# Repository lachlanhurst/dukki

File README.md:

# Dukki

> [!IMPORTANT]
> Everything in here is very much a work in progress!

A rework of the Pollen Robotics [Microduck](https://github.com/pollen-robotics/microduck) with a few hardware changes:

- Radxa CM4 brain (instead of the Radxa Zero 3W)
  - RK3576 vs RK3566: roughly twice the CPU and a 6 TOPS NPU vs 0.8 TOPS
- Unitree J288 servos (instead of the Dynamixel XL330-M288-T)
  - About three times faster: 35 rad/s (25 V), vs about 11 rad/s for the XL330
  - Twice the weight: 39 g vs 18 g
  - Similar stall torque, about 0.45 N·m measured against 0.43 N·m for the XL330 model

## Hardware block diagram

## What's in this repository

This repository holds the Dukki documentation, the hardware design files (KiCad), and the code that doesn't fit neatly into one of the forked repos, such as the STM32 servo bridge firmware, compute module setup scripts and J288 bench test tools. Changes elsewhere live on branches of forked repos: the robot firmware in [microduck](https://github.com/lachlanhurst/microduck/tree/dukki) (`dukki`), RL training in [microduck_rl](https://github.com/lachlanhurst/microduck_rl/tree/dukki-j288) (`dukki-j288`), the J288 actuator model in [bam](https://github.com/lachlanhurst/bam/tree/unitree-j288) (`unitree-j288`) and the head IMU driver in [bmi088-rs](https://github.com/lachlanhurst/bmi088-rs/tree/configurable-addresses) (`configurable-addresses`).

## Docs

[Hardware](docs/hardware.md) is the main design document. It covers each subsystem (servos, compute, the STM32 servo bridge, IMUs, power, audio, camera, ToF) and compares it with the OG robot.

[Compute setup](docs/compute-setup.md) takes a Radxa CM4 from the box to a board on WiFi at `microduck.local`. That includes flashing Armbian to the eMMC.

[Servo setup](docs/motor-setup.md) is the bench procedure for each J288 before assembly. You set the bus ID with Unitree's Windows tool, record the firmware version, run a motion check and label the servo for its joint.

[J288 bench testing](docs/j288-testing.md) has the results from characterising one servo: bus timing, friction, armature, torque limits and heating. The main finding is that peak output torque is about 0.45 N·m, close to the XL330.

[Camera setup](docs/camera-setup.md) and [audio setup](docs/audio-setup.md) bring up the IMX219 camera and the MAX98357A speaker and INMP441 microphone on the CM4.

## Licence

MIT, see [LICENSE](LICENSE). The third-party datasheets and schematics in [docs/datasheets/](docs/datasheets/) belong to their publishers and are not covered by it.

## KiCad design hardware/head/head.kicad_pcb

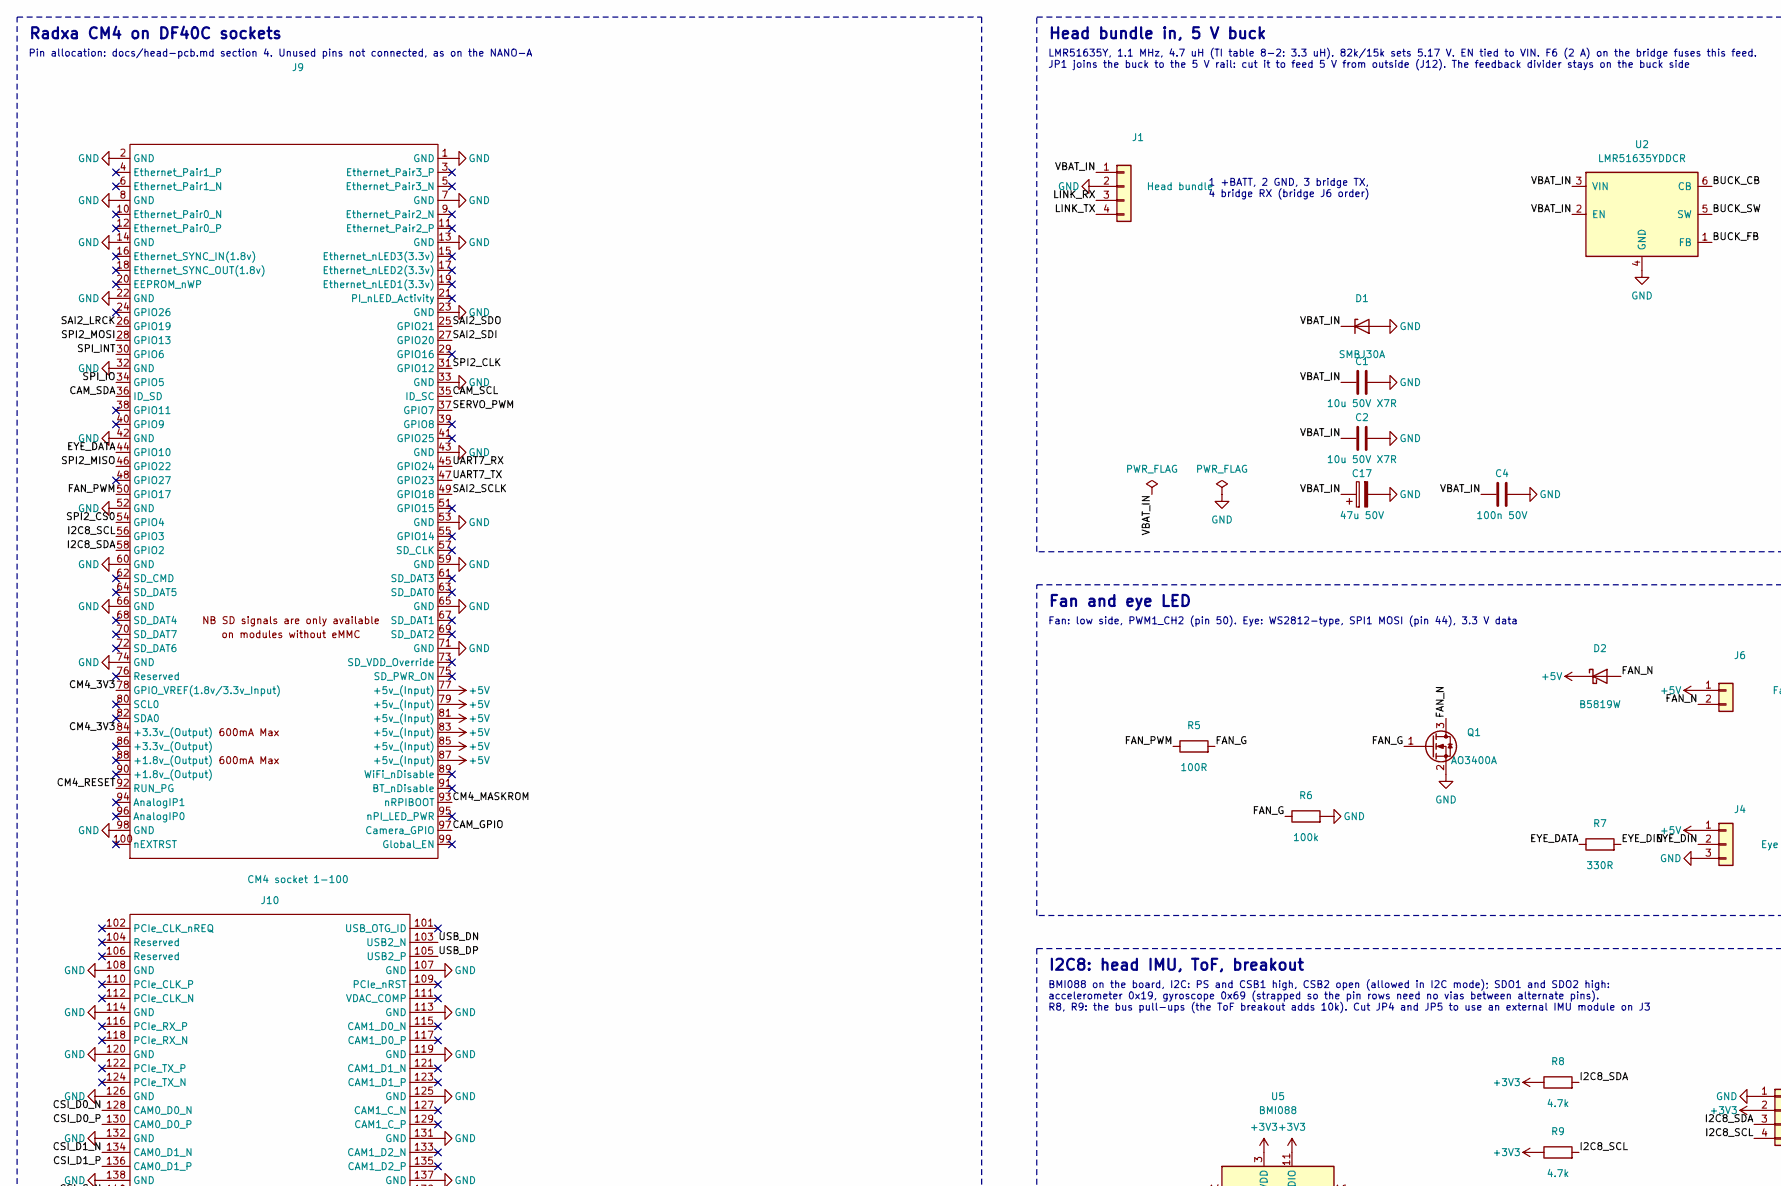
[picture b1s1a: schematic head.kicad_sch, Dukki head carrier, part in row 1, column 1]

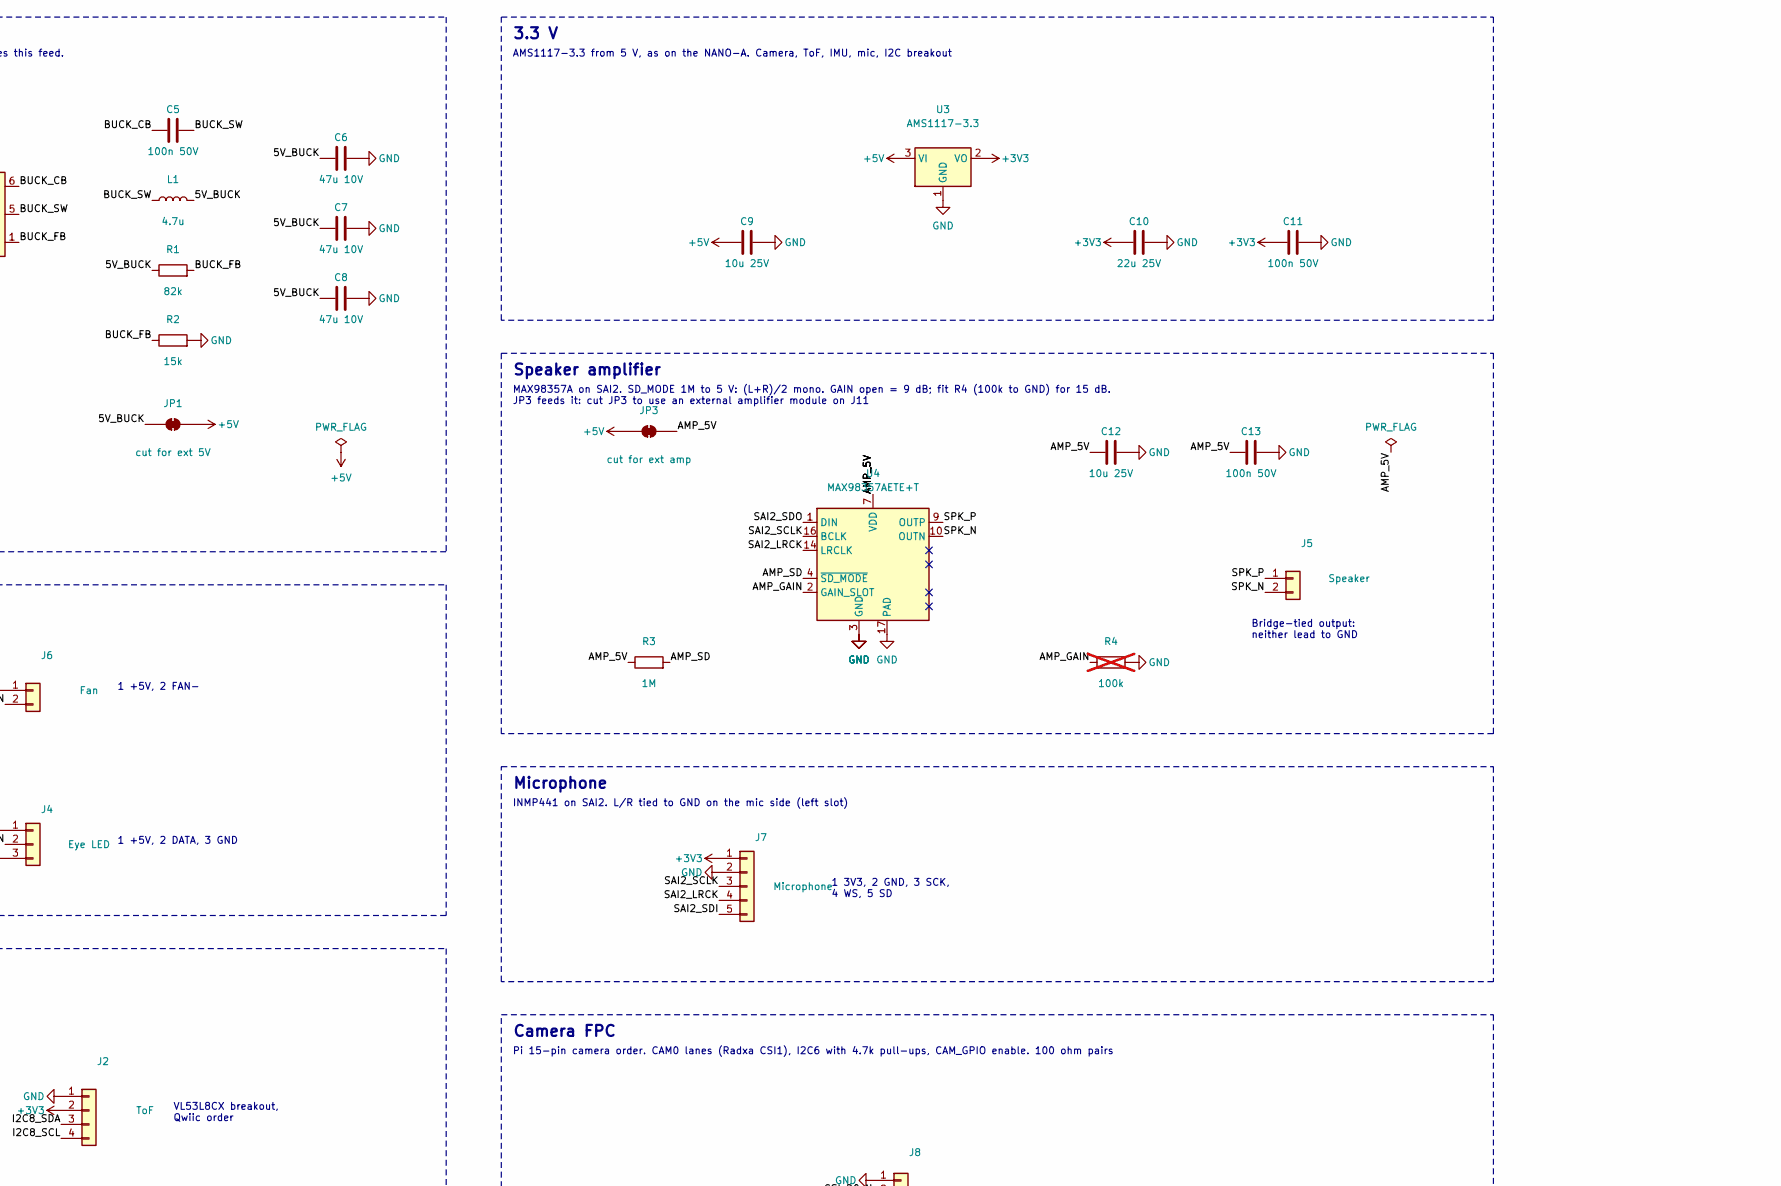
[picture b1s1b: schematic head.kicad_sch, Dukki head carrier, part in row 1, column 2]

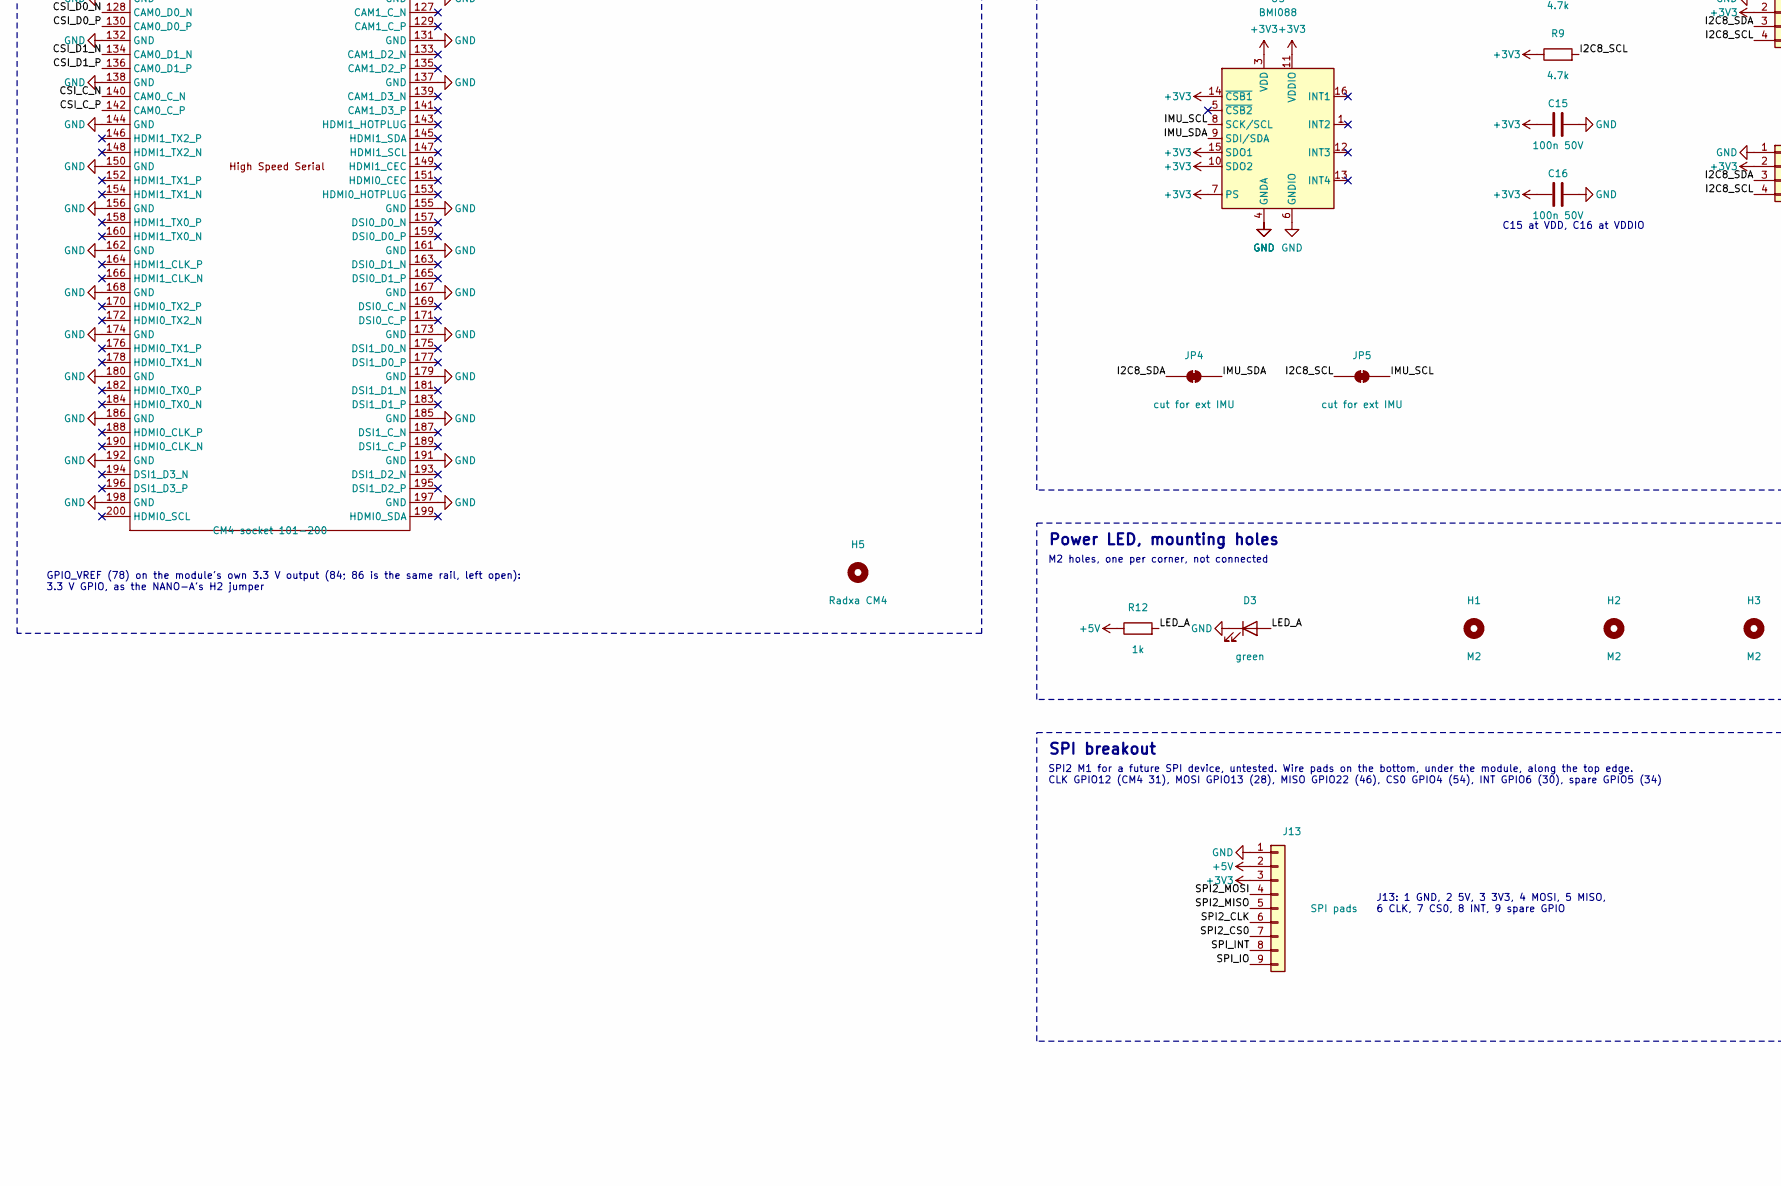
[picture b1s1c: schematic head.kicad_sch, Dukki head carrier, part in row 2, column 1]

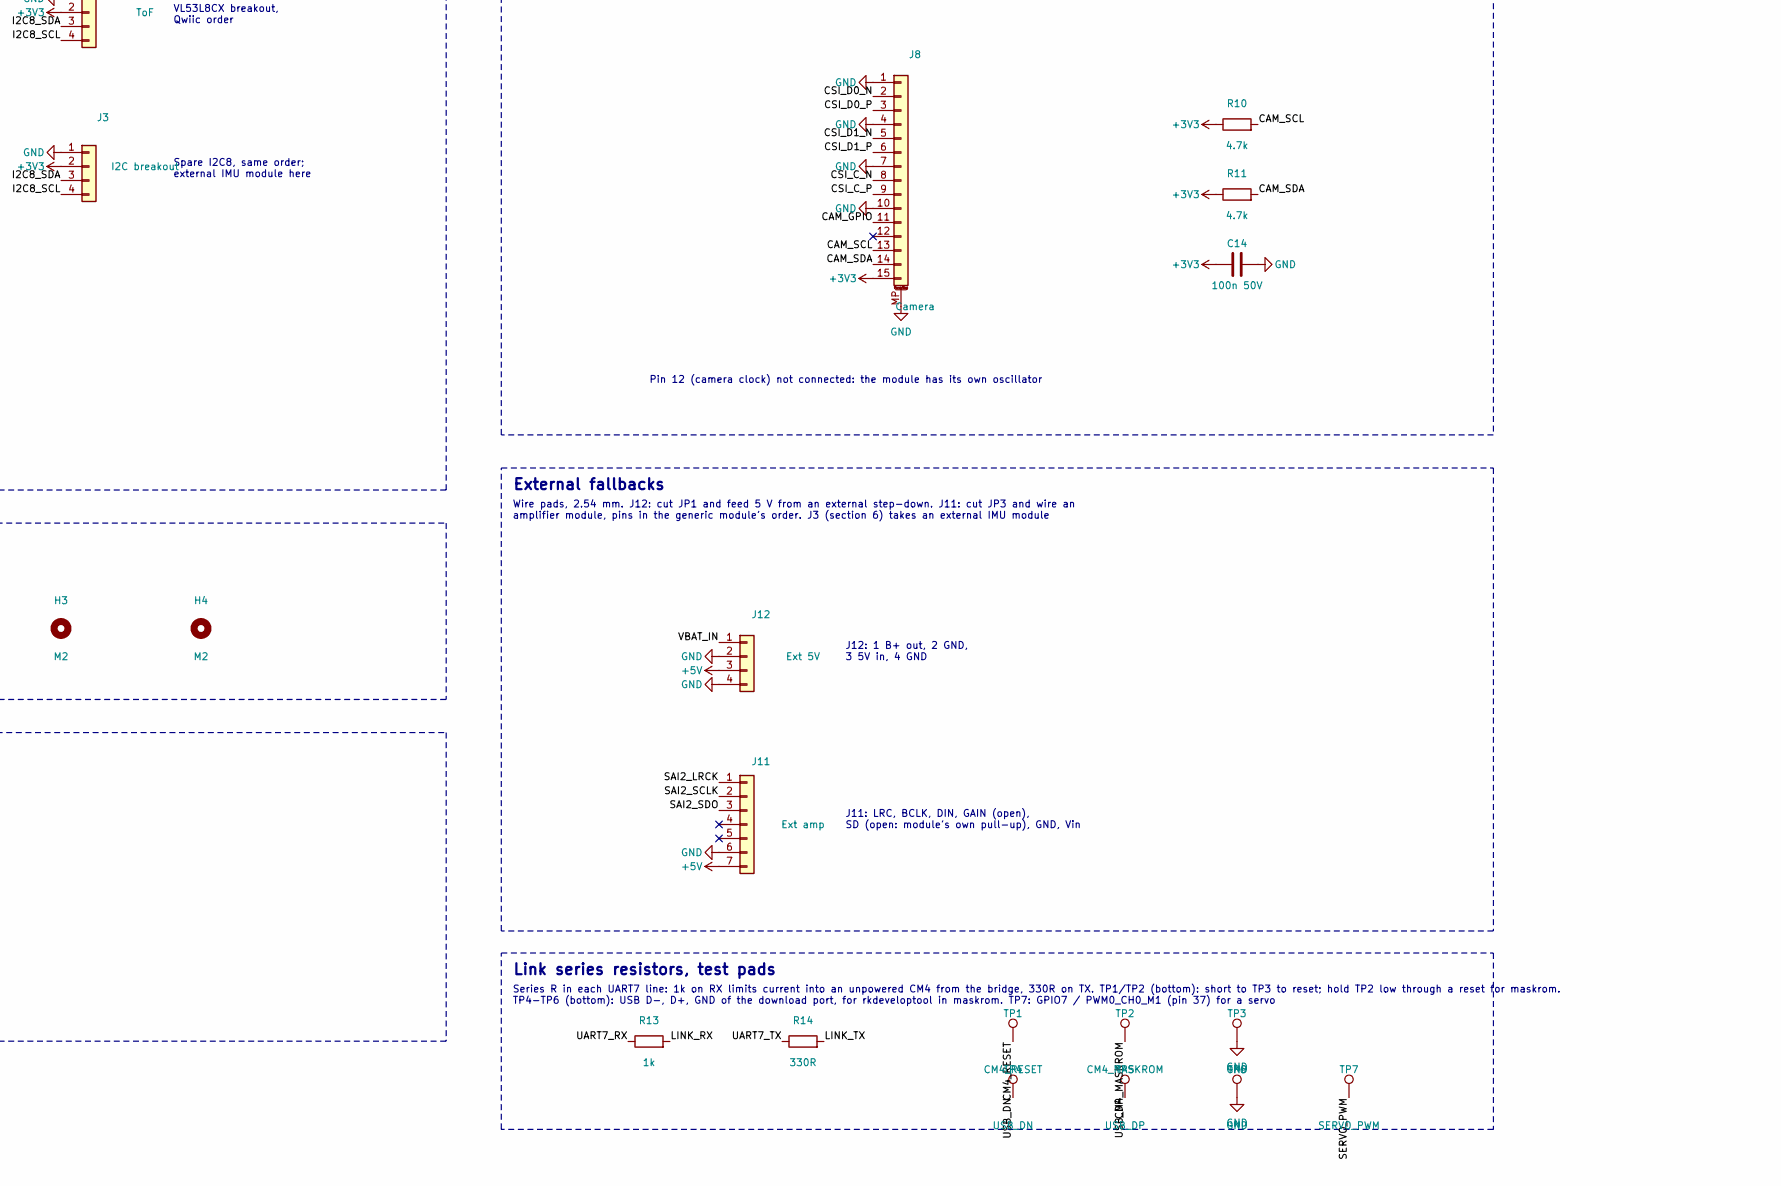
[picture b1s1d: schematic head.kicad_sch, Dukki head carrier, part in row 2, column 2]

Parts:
C1, C2: 10u 50V X7R; C_1210_3225Metric; LCSC C596319
C4, C5, C11, C13, C14, C15, C16: 100n 50V; C_0603_1608Metric; LCSC C14663
C6, C7, C8: 47u 10V; C_1206_3216Metric; LCSC C96123
C9, C12: 10u 25V; C_0805_2012Metric; LCSC C15850
C10: 22u 25V; C_0805_2012Metric; LCSC C45783
C17: 47u 50V; CP_Elec_6.3x7.7; MPN RVT1H470M0607, 47 uF 50 V aluminium, 6.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; LCSC C970679
D1: SMBJ30A; D_SMB; LCSC C19077584
D2: B5819W; D_SOD-123; LCSC C8598
D3: green; LED_0603_1608Metric; LCSC C12624
H1, H2, H3, H4: M2; MountingHole_2.2mm_M2
H5: Radxa CM4; Radxa_CM4_Module
J1: Head bundle; JST_PH_B4B-PH-K_1x04_P2.00mm_Vertical; MPN JST B4B-PH-K-S, through hole, fitted by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
J2: ToF; JST_PH_B4B-PH-K_1x04_P2.00mm_Vertical; MPN JST B4B-PH-K-S, through hole, fitted by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
J3: I2C breakout; JST_PH_B4B-PH-K_1x04_P2.00mm_Vertical; MPN JST B4B-PH-K-S, through hole, fitted by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
J4: Eye LED; JST_PH_B3B-PH-K_1x03_P2.00mm_Vertical; MPN JST B3B-PH-K-S, through hole, fitted by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
J5: Speaker; JST_PH_B2B-PH-K_1x02_P2.00mm_Vertical; MPN JST B2B-PH-K-S, through hole, fitted by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
J6: Fan; JST_PH_B2B-PH-K_1x02_P2.00mm_Vertical; MPN JST B2B-PH-K-S, through hole, fitted by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
J7: Microphone; JST_PH_B5B-PH-K_1x05_P2.00mm_Vertical; MPN JST B5B-PH-K-S, through hole, fitted by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
J8: Camera; FPC_XUNPU_FPC-1.0HF-15PWAR-H20_1x15-1MP_P1.0mm; MPN XUNPU FPC-1.0HF-15PWAR-H20, dual contact; LCSC C19269369
J9: CM4 socket 1-100; DF40C_Socket_CM4_1-100; MPN Hirose DF40C-100DS-0.4V(51); LCSC C597931
J10: CM4 socket 101-200; DF40C_Socket_CM4_101-200; MPN Hirose DF40C-100DS-0.4V(51); LCSC C597931
J11: Ext amp; PinHeader_1x07_P2.54mm_Vertical
J12: Ext 5V; PinHeader_1x04_P2.54mm_Vertical
J13: SPI pads; SolderPads_1x09_P2.54mm_SPI
JP1: cut for ext 5V; SolderJumper-2_Wide_Bridged_3A
JP3: cut for ext amp; SolderJumper-2_Wide_Bridged_3A
JP4, JP5: cut for ext IMU; SolderJumper-2_P1.3mm_Bridged_RoundedPad1.0x1.5mm
L1: 4.7u; L_Sunlord_SWPA6045S; MPN Sunlord SWPA6045S4R7MT, 4.7 uH, 5.5 A s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; LCSC C78804
Q1: AO3400A; SOT-23; LCSC C20917
R1: 82k; R_0603_1608Metric; LCSC C23254
R2: 15k; R_0603_1608Metric; LCSC C22809
R3: 1M; R_0603_1608Metric; LCSC C22935
R4: 100k; R_0603_1608Metric; LCSC C25803; not fitted
R5: 100R; R_0603_1608Metric; LCSC C22775
R6: 100k; R_0603_1608Metric; LCSC C25803
R7, R14: 330R; R_0603_1608Metric; LCSC C23138
R8, R9, R10, R11: 4.7k; R_0603_1608Metric; LCSC C23162
R12, R13: 1k; R_0603_1608Metric; LCSC C21190
TP1: CM4_RESET; TestPoint_Pad_D1.5mm
TP2: CM4_MASKROM; TestPoint_Pad_D1.5mm
TP3, TP6: GND; TestPoint_Pad_D1.5mm
TP4: USB_DN; TestPoint_Pad_D1.5mm
TP5: USB_DP; TestPoint_Pad_D1.5mm
TP7: SERVO_PWM; TestPoint_Pad_D1.5mm
U2: LMR51635YDDCR; TSOT-23-6; LCSC C45262770
U3: AMS1117-3.3; SOT-223-3_TabPin2; LCSC C6186
U4: MAX98357AETE+T; TQFN-16-1EP_3x3mm_P0.5mm_EP1.23x1.23mm; LCSC C910544
U5: BMI088; Bosch_LGA-16_4.5x3mm_P0.5mm_LayoutBorder7x1y_ClockwisePinNu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; LCSC C194919

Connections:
+3V3: C10.1, C11.1, C14.1, C15.1, C16.1, J2.2, J3.2, J7.1, J8.15, J13.3, R8.1, R9.1, R10.1, R11.1, U3.2 (VO), U5.3 (VDD), U5.7 (PS), U5.10 (SDO2), U5.11 (VDDIO), U5.14 (~CSB1), U5.15 (SDO1)
+5V: C9.1, D2.1 (K), J4.1, J6.1, J9.77 (+5v_(Input)), J9.79 (+5v_(Input)), J9.81 (+5v_(Input)), J9.83 (+5v_(Input)), J9.85 (+5v_(Input)), J9.87 (+5v_(Input)), J11.7, J12.3, J13.2, JP1.2 (B), JP3.1 (A), R12.1, U3.3 (VI)
/5V_BUCK: C6.1, C7.1, C8.1, JP1.1 (A), L1.2, R1.1
/AMP_5V: C12.1, C13.1, JP3.2 (B), R3.1, U4.7 (VDD), U4.8 (VDD)
/AMP_GAIN: R4.1, U4.2 (GAIN_SLOT)
/AMP_SD: R3.2, U4.4 (~SD_MODE)
/BUCK_CB: C5.1, U2.6 (CB)
/BUCK_FB: R1.2, R2.1, U2.1 (FB)
/BUCK_SW: C5.2, L1.1, U2.5 (SW)
/CAM_GPIO: J8.11, J9.97 (Camera_GPIO)
/CAM_SCL: J8.13, J9.35 (ID_SC), R10.2
/CAM_SDA: J8.14, J9.36 (ID_SD), R11.2
/CM4_3V3: J9.78 (GPIO_VREF(1.8v/3.3v_Input)), J9.84 (+3.3v_(Output))
/CM4_MASKROM: J9.93 (nRPIBOOT), TP2.1
/CM4_RESET: J9.92 (RUN_PG), TP1.1
/CSI_C_N: J8.8, J10.140 (CAM0_C_N)
/CSI_C_P: J8.9, J10.142 (CAM0_C_P)
/CSI_D0_N: J8.2, J10.128 (CAM0_D0_N)
/CSI_D0_P: J8.3, J10.130 (CAM0_D0_P)
/CSI_D1_N: J8.5, J10.134 (CAM0_D1_N)
/CSI_D1_P: J8.6, J10.136 (CAM0_D1_P)
/EYE_DATA: J9.44 (GPIO10), R7.1
/EYE_DIN: J4.2, R7.2
/FAN_G: Q1.1 (G), R5.2, R6.1
/FAN_N: D2.2 (A), J6.2, Q1.3 (D)
/FAN_PWM: J9.50 (GPIO17), R5.1
/I2C8_SCL: J2.4, J3.4, J9.56 (GPIO3), JP5.1 (A), R9.2
/I2C8_SDA: J2.3, J3.3, J9.58 (GPIO2), JP4.1 (A), R8.2
/IMU_SCL: JP5.2 (B), U5.8 (SCK/SCL)
/IMU_SDA: JP4.2 (B), U5.9 (SDI/SDA)
/LED_A: D3.2 (A), R12.2
/LINK_RX: J1.3, R13.2
/LINK_TX: J1.4, R14.2
/SAI2_LRCK: J7.4, J9.26 (GPIO19), J11.1, U4.14 (LRCLK)
/SAI2_SCLK: J7.3, J9.49 (GPIO18), J11.2, U4.16 (BCLK)
/SAI2_SDI: J7.5, J9.27 (GPIO20)
/SAI2_SDO: J9.25 (GPIO21), J11.3, U4.1 (DIN)
/SERVO_PWM: J9.37 (GPIO7), TP7.1
/SPI2_CLK: J9.31 (GPIO12), J13.6
/SPI2_CS0: J9.54 (GPIO4), J13.7
/SPI2_MISO: J9.46 (GPIO22), J13.5
/SPI2_MOSI: J9.28 (GPIO13), J13.4
/SPI_INT: J9.30 (GPIO6), J13.8
/SPI_IO: J9.34 (GPIO5), J13.9
/SPK_N: J5.2, U4.10 (OUTN)
/SPK_P: J5.1, U4.9 (OUTP)
/UART7_RX: J9.45 (GPIO24), R13.1
/UART7_TX: J9.47 (GPIO23), R14.1
/USB_DN: J10.103 (USB2_N), TP4.1
/USB_DP: J10.105 (USB2_P), TP5.1
/VBAT_IN: C1.1, C2.1, C4.1, C17.1, D1.1 (K), J1.1, J12.1, U2.2 (EN), U2.3 (VIN)
GND: C1.2, C2.2, C4.2, C6.2, C7.2, C8.2, C9.2, C10.2, C11.2, C12.2, C13.2, C14.2, C15.2, C16.2, C17.2, D1.2 (A), D3.1 (K), J1.2, J2.1, J3.1, J4.3, J7.2, J8.1, J8.4, J8.7, J8.10, J8.MP (MountPin), J9.1 (GND), J9.2 (GND), J9.7 (GND), J9.8 (GND), J9.13 (GND), J9.14 (GND), J9.22 (GND), J9.23 (GND), J9.32 (GND), J9.33 (GND), J9.42 (GND), J9.43 (GND), J9.52 (GND), J9.53 (GND), J9.59 (GND), J9.60 (GND), J9.65 (GND), J9.66 (GND), J9.71 (GND), J9.74 (GND), J9.98 (GND), J10.107 (GND), J10.108 (GND), J10.113 (GND), J10.114 (GND), J10.119 (GND), J10.120 (GND), J10.125 (GND), J10.126 (GND), J10.131 (GND), J10.132 (GND), J10.137 (GND), J10.138 (GND), J10.144 (GND), J10.150 (GND), J10.155 (GND), J10.156 (GND), J10.161 (GND), J10.162 (GND), J10.167 (GND), J10.168 (GND), J10.173 (GND), J10.174 (GND), J10.179 (GND), J10.180 (GND), J10.185 (GND), J10.186 (GND), J10.191 (GND), J10.192 (GND), J10.197 (GND), J10.198 (GND), J11.6, J12.2, J12.4, J13.1, Q1.2 (S), R2.2, R4.2, R6.2, TP3.1, TP6.1, U2.4 (GND), U3.1 (GND), U4.3 (GND), U4.11 (GND), U4.15 (GND), U4.17 (PAD), U5.2 (GNDA), U5.4 (GNDA), U5.6 (GNDIO)

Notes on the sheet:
Radxa CM4 on DF40C sockets
Pin allocation: docs/head-pcb.md section 4. Unused pins not connected, as on the NANO-A
GPIO_VREF (78) on the module's own 3.3 V output (84; 86 is the same rail, left open): 3.3 V GPIO, as the NANO-A's H2 jumper
Head bundle in, 5 V buck
LMR51635Y, 1.1 MHz, 4.7 uH (TI table 8-2: 3.3 uH). 82k/15k sets 5.17 V. EN tied to VIN. F6 (2 A) on the bridge fuses this feed. JP1 joins the buck to the 5 V rail: cut it to feed 5 V from outside (J12). The feedback divider stays on the buck side
1 +BATT, 2 GND, 3 bridge TX, 4 bridge RX (bridge J6 order)
3.3 V
AMS1117-3.3 from 5 V, as on the NANO-A. Camera, ToF, IMU, mic, I2C breakout
Speaker amplifier
MAX98357A on SAI2. SD_MODE 1M to 5 V: (L+R)/2 mono. GAIN open = 9 dB; fit R4 (100k to GND) for 15 dB. JP3 feeds it: cut JP3 to use an external amplifier module on J11
Bridge-tied output: neither lead to GND
Fan and eye LED
Fan: low side, PWM1_CH2 (pin 50). Eye: WS2812-type, SPI1 MOSI (pin 44), 3.3 V data
1 +5V, 2 FAN-
1 +5V, 2 DATA, 3 GND
I2C8: head IMU, ToF, breakout
BMI088 on the board, I2C: PS and CSB1 high, CSB2 open (allowed in I2C mode); SDO1 and SDO2 high: accelerometer 0x19, gyroscope 0x69 (strapped so the pin rows need no vias between alternate pins). R8, R9: the bus pull-ups (the ToF breakout adds 10k). Cut JP4 and JP5 to use an external IMU module on 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
C15 at VDD, C16 at VDDIO
VL53L8CX breakout, Qwiic order
Spare I2C8, same order; external IMU module here
Microphone
INMP441 on SAI2. L/R tied to GND on the mic side (left slot)
1 3V3, 2 GND, 3 SCK, 4 WS, 5 SD
Camera FPC
Pi 15-pin camera order. CAM0 lanes (Radxa CSI1), I2C6 with 4.7k pull-ups, CAM_GPIO enable. 100 ohm pairs
Pin 12 (camera clock) not connected: the module has its own oscillator
Power LED, mounting holes
M2 holes, one per corner, not connected
External fallbacks
Wire pads, 2.54 mm. J12: cut JP1 and feed 5 V from an external step-down. J11: cut JP3 and wire an amplifier module, pins in the generic module's order. J3 (section 6) takes an external IMU module
J12: 1 B+ out, 2 GND, 3 5V in, 4 GND
J11: LRC, BCLK, DIN, GAIN (open), SD (open: module's own pull-up), GND, Vin
SPI breakout
SPI2 M1 for a future SPI device, untested. Wire pads on the bottom, under the module, along the top edge. CLK GPIO12 (CM4 31), MOSI GPIO13 (28), MISO GPIO22 (46), CS0 GPIO4 (54), INT GPIO6 (30), spare GPIO5 (34)
J13: 1 GND, 2 5V, 3 3V3, 4 MOSI, 5 MISO, 6 CLK, 7 CS0, 8 INT, 9 spare GPIO
Link series resistors, test pads
Series R in each UART7 line: 1k on RX limits current into an unpowered CM4 from the bridge, 330R on TX. TP1/TP2 (bottom): short to TP3 to reset; hold TP2 low through a reset for maskrom. TP4-TP6 (bottom): USB D-, D+, GND of the download port, for rkdeveloptool in maskrom. TP7: GPIO7 / PWM0_CH0_M1 (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

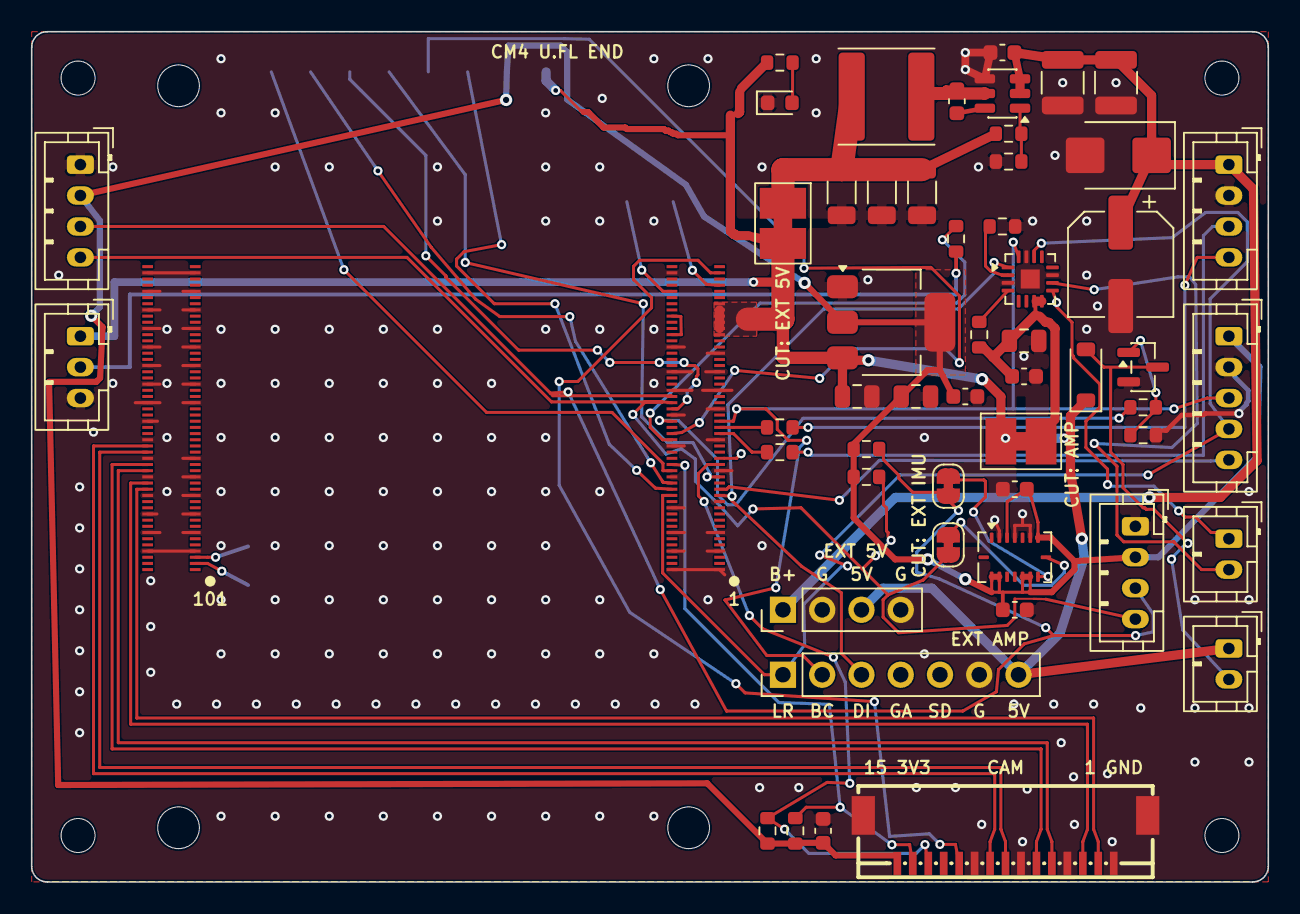
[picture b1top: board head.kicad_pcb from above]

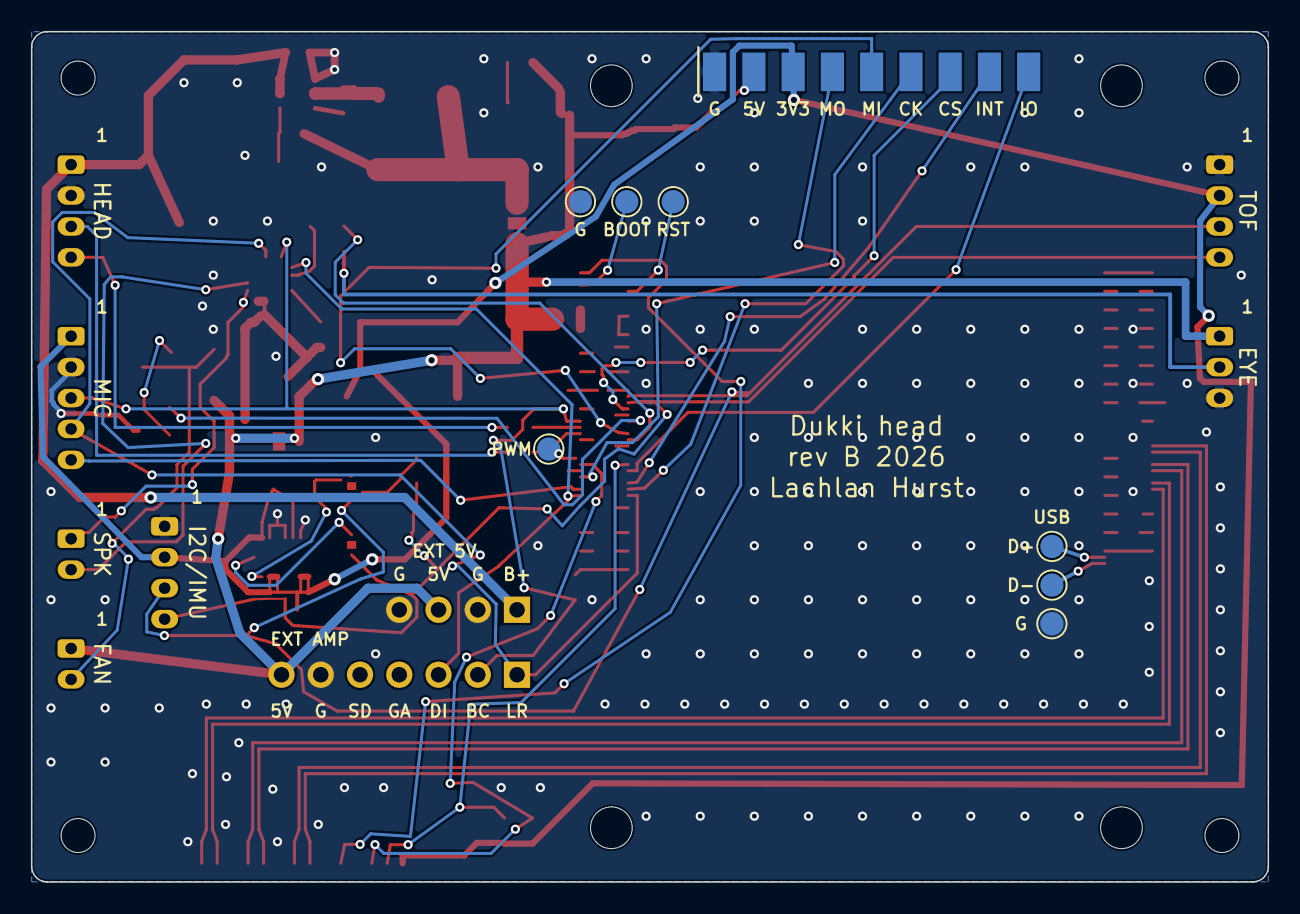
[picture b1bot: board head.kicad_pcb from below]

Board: 2 copper layers, 80.0 x 55.0 mm, 68 parts (8 on the bottom side), 52 nets.

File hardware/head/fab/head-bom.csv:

Comment,Designator,Footprint,LCSC Part #
10u 50V X7R,"C1,C2",C_1210_3225Metric,C596319
100n 50V,"C4,C5,C11,C13,C14,C15,C16",C_0603_1608Metric,C14663
47u 10V,"C6,C7,C8",C_1206_3216Metric,C96123
10u 25V,"C9,C12",C_0805_2012Metric,C15850
22u 25V,C10,C_0805_2012Metric,C45783
47u 50V,C17,CP_Elec_6.3x7.7,C970679
SMBJ30A,D1,D_SMB,C19077584
B5819W,D2,D_SOD-123,C8598
green,D3,LED_0603_1608Metric,C12624
Camera,J8,FPC_XUNPU_FPC-1.0HF-15PWAR-H20_1x15-1MP_P1.0mm,C19269369
CM4 socket 1-100,J9,DF40C_Socket_CM4_1-100,C597931
CM4 socket 101-200,J10,DF40C_Socket_CM4_101-200,C597931
4.7u,L1,L_Sunlord_SWPA6045S,C78804
AO3400A,Q1,SOT-23,C20917
82k,R1,R_0603_1608Metric,C23254
15k,R2,R_0603_1608Metric,C22809
1M,R3,R_0603_1608Metric,C22935
100R,R5,R_0603_1608Metric,C22775
100k,R6,R_0603_1608Metric,C25803
330R,"R7,R14",R_0603_1608Metric,C23138
4.7k,"R8,R9,R10,R11",R_0603_1608Metric,C23162
1k,"R12,R13",R_0603_1608Metric,C21190
LMR51635YDDCR,U2,TSOT-23-6,C45262770
AMS1117-3.3,U3,SOT-223-3_TabPin2,C6186
MAX98357AETE+T,U4,TQFN-16-1EP_3x3mm_P0.5mm_EP1.23x1.23mm,C910544
BMI088,U5,Bosch_LGA-16_4.5x3mm_P0.5mm_LayoutBorder7x1y_ClockwisePinNumbering,C194919
